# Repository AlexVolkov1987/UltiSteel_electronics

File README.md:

# UltiSteel_electronics
Electronics update for Ulti Steel 3D printer

------

:warning: Автор не несет ответственности за неправильную сборку, выбор комплектующих и любую порчу имущества и здоровья, вызванную эксплуатацией описываемых плат.

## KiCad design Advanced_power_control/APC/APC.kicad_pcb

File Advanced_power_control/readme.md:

# Модуль управления и мониторинга питания принтера

## Описание

### Функции:

- Включение принтера с помощью тактовой кнопки включение
- Выключение принтера по команде с платы управления принтера
- Выключение принтера с помощью тактовой кнопки включения
- Аварийное отключение принтера по команде с платы управления принтера
- Аварийное отключение принтера с помощью внешней кнопки
- Аварийное отключение принтера по КЗ или потере напряжения в линии питания 12/24В

### Разъемы:

- 220_IN - высоковольтный вход модуля. Должен всегда находиться под напряжением
- 220_OUT - управляемый выход модуля. К нему подключается высоковольтный вход блока питания принтера
- POWER_BUTTON - тактовая кнопка для включения/выключения модуля
- POWER_LED - индикация наличия питания на выходе блока питания принтера.
- STATUS_LED - индикация состояния принтера  
- EM_STOP - тактовая кнопка аварийной остановки. Должна быть нормально замкнутой. В случае отсутствия кнопки, для нормальной работы модуля необходимо установить перемычку EM_INT.
- 12/24 V_IN - мониторинг низковольтного выхода блока питания принтера
- CMD_IN - вход управления модулем от управляющей платы принтера.
- CMD_OUT - выход модуля для передачи информации на управляющую плату принтера

### Описание работы:

#### Установка

Установка модуля производится согласно схеме подключения ниже:

Если установка модуля выполнена корректно, то при подаче питания 220В модуль выдаст два коротких звуковых сигнала и включит индикатор STATUS_LED на 5 секунд. В дальнейшем индикатор STATUS_LED будет включаться на 1 секунду каждые 10с в качестве признака состояния сна модуля.

#### Первое включение (по нажатию тактовой кнопки POWER_BUTTON)

Включение модуля производится удержанием тактовой кнопки включения в течение 3-4с.  Модуль выдаст короткий звуковой сигнал и напряжение 220В будет подано на вход блока питания принтера. После этого индикатор STATUS_LED начнет мигать 1 раз в секунду. Таким образом, модуль перешел из состояния сна с состояние ожидания.

В течение минуты после подачи питания управляющая плата принтера должна подать напряжение на разъем модуля CMD_IN. Если этого не произойдет - модуль отключит подачу питания на вход блока питания принтера, выдаст три звуковых сигнала и перейдет из состояния ожидания в состояние сна.

При появлении напряжения на разъеме CMD_IN во время нахождения модуля в состоянии ожидания модуль выдаст один короткий звуковой сигнал, а индикатор  STATUS_LED будет светиться непрерывно. Модуль при этом перейдет в состояние активности.

! В процессе включения и выключения, а так же работы индикатор POWER_LED может включаться и выключаться с запаздыванием, поскольку он отображает наличие напряжения на выходе блока питания принтера и никак не управляется модулем.

#### Выключение (по нажатию кнопки POWER_BUTTON)

 При кратковременном нажатии кнопки POWER_BUTTON модуль управления питанием активирует выход CMD_OUT. Прошивка материнской платы должна использовать этот факт как выполнение последовательности команд по остановке печати, охлаждению хотэнда и снятию сигнала активности с входа CMD_IN.

Если плата снимает напряжение с входа CMD_IN, модуль выдаст двойной короткий звуковой сигнал и через 10с снимет напряжение с блока питания принтера, перейдя в состояние сна.

#### Выключение (по удержанию кнопки POWER_BUTTON)

При удержании кнопки POWER_BUTTON в течение 5-6с модуль снимает напряжение с блока питания принтера и переходит в состояние сна

#### Выключение по команде M81

Управляющая плата при выполнении команды M81 должна снять напряжение с входа CMD_IN модуля. Реакция модуля будет такой же как в варианте выключения по нажатию кнопки POWER_BUTTON.

#### Аварийное выключение по размыканию кнопки EM_STOP

При размыкании кнопки EM_STOP модуль немедленно снимает питание с блока питания принтера. Индикатор STATUS_LED при этом мигает с частотой 3 раза в секунду.

Также блокируется включение принтера по нажатию кнопки POWER_BUTTON. Для снятия блокировки необходимо замкнуть контакты кнопки  EM_STOP. Модуль при этом перейдет в состояние сна.

#### Аварийное выключение по потере напряжения 12/24В

Если в режиме активности на вход 12/24 V_IN не поступает напряжение с блока питания принтера (КЗ или выход из строя блока питания принтера), модуль немедленно снимает напряжение с входа блока питания принтера и выдает три длинных звуковых сигнала.  Индикатор STATUS_LED при этом мигает с частотой 3 раза в секунду.

Также блокируется включение принтера по нажатию кнопки POWER_BUTTON. Для снятия блокировки необходимо полностью обесточить модуль на 30-60сек.

### Список основных компонентов:

- ATMEGA164PA-AUR - микроконтроллер

- G5LE-14-DC5 - силовое реле

- LTV-817A - опторазвязка

- DG126-5.0-03P-14-00AH - клеммник

- IRM-03-5 - изолированный источник питания

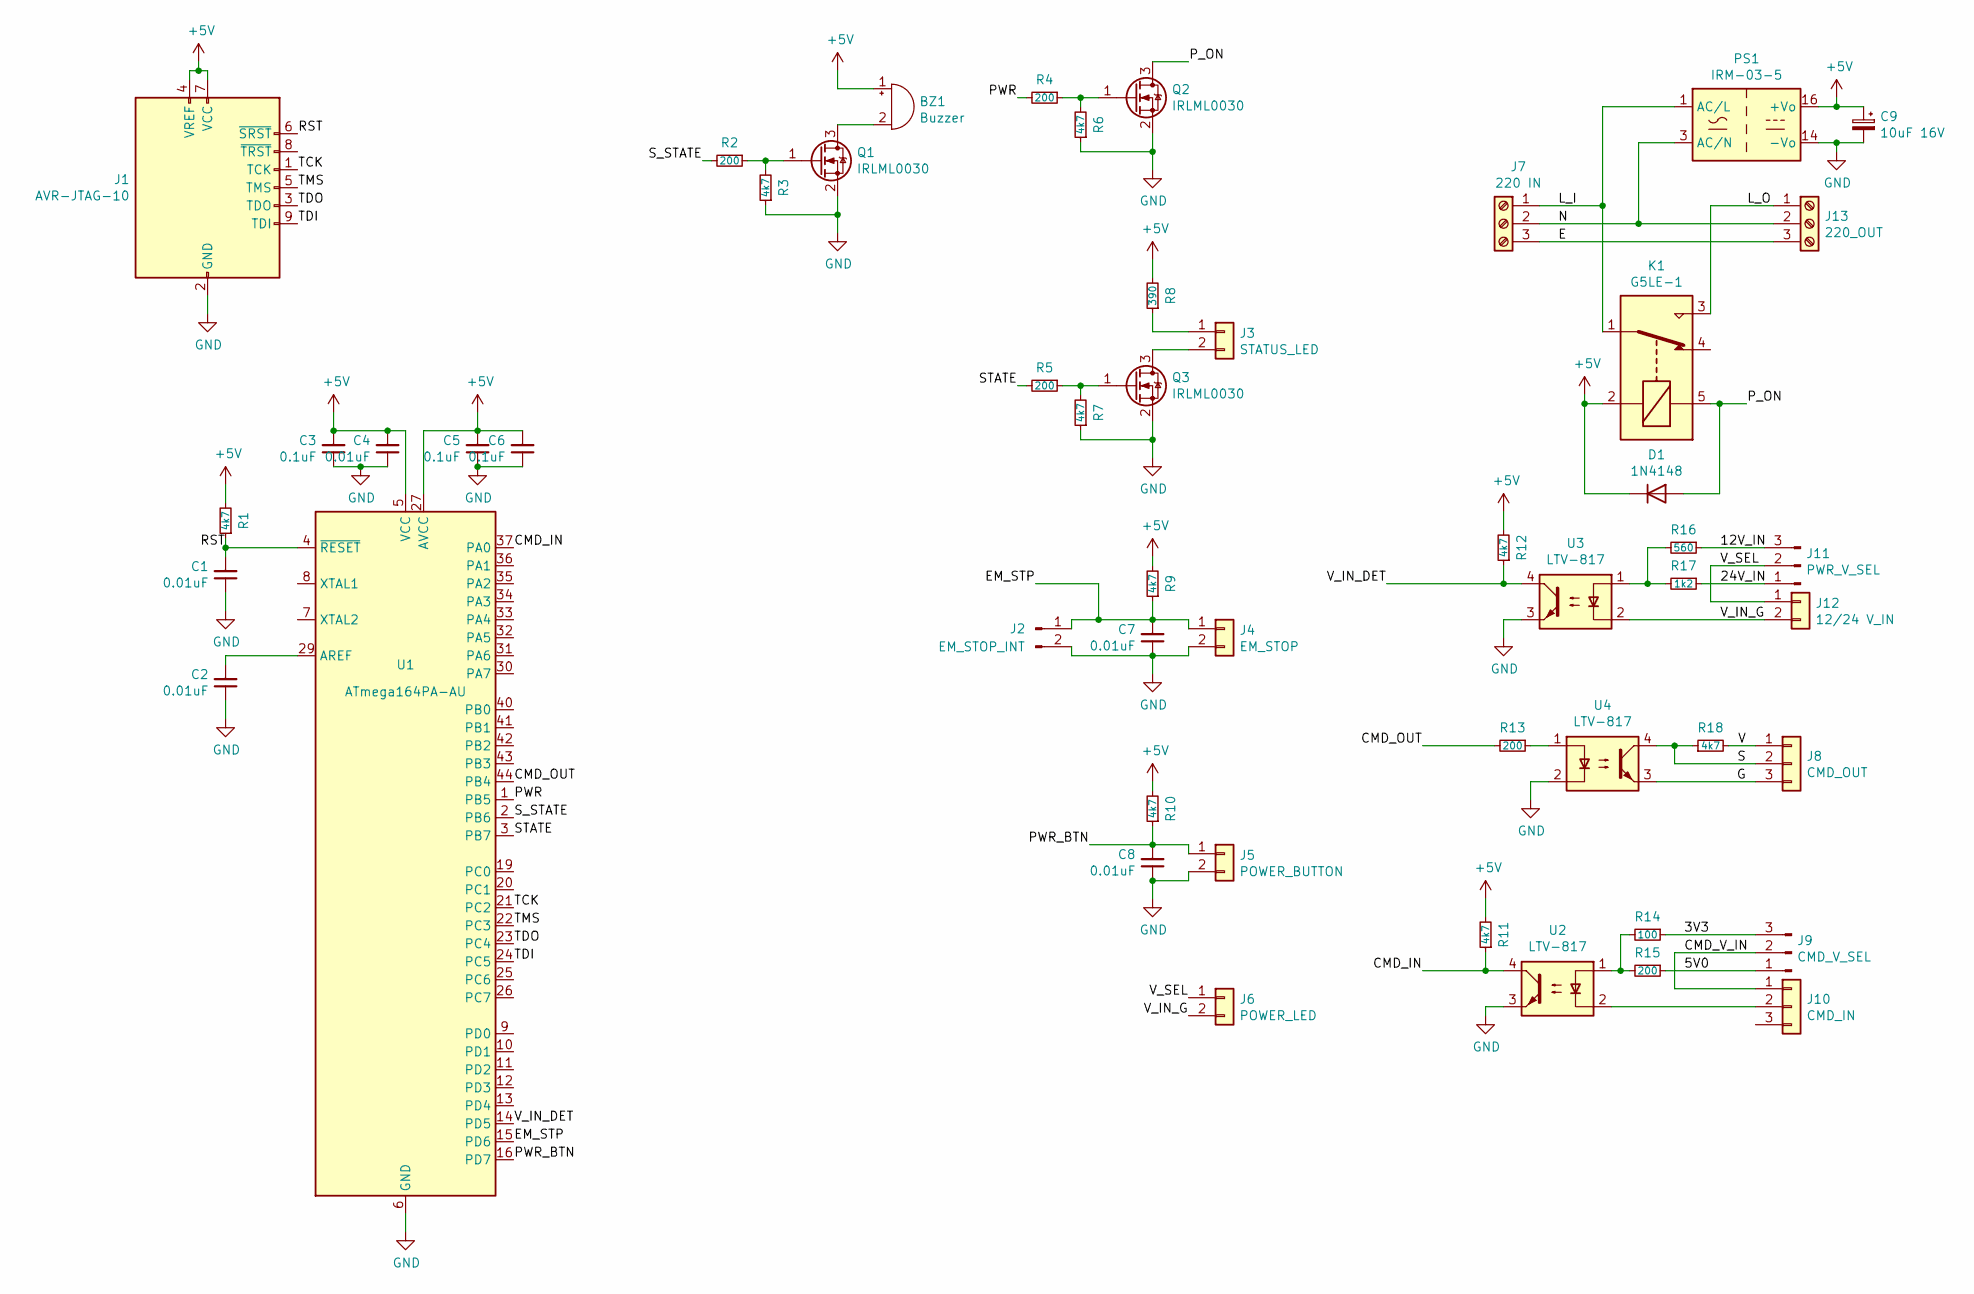
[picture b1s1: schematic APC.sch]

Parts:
BZ1: Buzzer; Buzzer_12x9.5RM7.6
C1, C2, C4, C7, C8: 0.01uF; C_0805_2012Metric_Pad1.15x1.40mm_HandSolder
C3, C5, C6: 0.1uF; C_0805_2012Metric_Pad1.15x1.40mm_HandSolder
C9: 10uF 16V; CP_EIA-3528-21_Kemet-B_Pad1.50x2.35mm_HandSolder
D1: 1N4148; D_DO-35_SOD27_P7.62mm_Horizontal
J1: AVR-JTAG-10; PinHeader_2x05_P2.54mm_Vertical
J2: EM_STOP_INT; PinHeader_1x02_P2.54mm_Vertical
J3: STATUS_LED; JST_EH_B2B-EH-A_1x02_P2.50mm_Vertical
J4: EM_STOP; JST_EH_B2B-EH-A_1x02_P2.50mm_Vertical
J5: POWER_BUTTON; JST_EH_B2B-EH-A_1x02_P2.50mm_Vertical
J6: POWER_LED; JST_EH_B2B-EH-A_1x02_P2.50mm_Vertical
J7: 220 IN; TerminalBlock_RND_205-00013_1x03_P5.00mm_Horizontal
J8: CMD_OUT; JST_EH_B3B-EH-A_1x03_P2.50mm_Vertical
J9: CMD_V_SEL; PinHeader_1x03_P2.54mm_Vertical
J10: CMD_IN; JST_EH_B3B-EH-A_1x03_P2.50mm_Vertical
J11: PWR_V_SEL; PinHeader_1x03_P2.54mm_Vertical
J12: 12/24 V_IN; JST_EH_B2B-EH-A_1x02_P2.50mm_Vertical
J13: 220_OUT; TerminalBlock_RND_205-00013_1x03_P5.00mm_Horizontal
K1: G5LE-1; Relay_SPDT_Omron-G5LE-1
PS1: IRM-03-5; Converter_ACDC_MeanWell_IRM-03-xx_THT
Q1, Q2, Q3: IRLML0030; SOT-23
R1, R3, R6, R7, R9, R10, R11, R12, R18: 4k7; R_0805_2012Metric_Pad1.20x1.40mm_HandSolder
R2, R4, R5, R13, R15: 200; R_0805_2012Metric_Pad1.20x1.40mm_HandSolder
R8: 390; R_0805_2012Metric_Pad1.20x1.40mm_HandSolder
R14: 100; R_0805_2012Metric_Pad1.20x1.40mm_HandSolder
R16: 560; R_0805_2012Metric_Pad1.20x1.40mm_HandSolder
R17: 1k2; R_0805_2012Metric_Pad1.20x1.40mm_HandSolder
U1: ATmega164PA-AU; TQFP-44_10x10mm_P0.8mm
U2, U3, U4: LTV-817; DIP-4_W7.62mm

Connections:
+5V: BZ1.1 (-), C3.2, C4.2, C5.2, C6.2, C9.1, D1.1 (K), J1.4 (VREF), J1.7 (VCC), K1.2, PS1.16 (+Vo), R1.2, R8.2, R9.2, R10.2, R11.2, R12.2, U1.5 (VCC), U1.17 (VCC), U1.27 (AVCC), U1.38 (VCC); also elsewhere on the board
/3V3: J9.3, R14.1
/5V0: J9.1, R15.1
/12V_IN: J11.3, R16.1
/24V_IN: J11.1, R17.1
/CMD_IN: R11.1, U1.37 (PA0), U2.4
/CMD_OUT: R13.2, U1.44 (PB4)
/CMD_V_IN: J9.2, J10.1
/E: J7.3, J13.3
/EM_STP: C7.2, J2.1, J4.1, R9.1, U1.15 (PD6)
/G: J8.3, U4.3
/L_I: J7.1, K1.1, PS1.1 (AC/L)
/L_O: J13.1, K1.3
/N: J7.2, J13.2, PS1.3 (AC/N)
/PWR: R4.2, U1.1 (PB5)
/PWR_BTN: C8.2, J5.1, R10.1, U1.16 (PD7)
/P_ON: D1.2 (A), K1.5, Q2.3 (D)
/RST: C1.2, J1.6 (~SRST), R1.1, U1.4 (~RESET); also elsewhere on the board
/S: J8.2, R18.1, U4.4
/STATE: R5.2, U1.3 (PB7)
/S_STATE: R2.2, U1.2 (PB6)
/TCK: J1.1 (TCK), U1.21 (PC2); also elsewhere on the board
/TDI: J1.9 (TDI), U1.24 (PC5); also elsewhere on the board
/TDO: J1.3 (TDO), U1.23 (PC4); also elsewhere on the board
/TMS: J1.5 (TMS), U1.22 (PC3); also elsewhere on the board
/V: J8.1, R18.2
/V_IN_DET: R12.1, U1.14 (PD5), U3.4
/V_IN_G: J6.2, J12.2, U3.2
/V_SEL: J6.1, J11.2, J12.1
GND: C1.1, C2.1, C3.1, C4.1, C5.1, C6.1, C7.1, C8.1, C9.2, J1.2 (GND), J1.10 (GND), J2.2, J4.2, J5.2, PS1.14 (-Vo), Q1.2 (S), Q2.2 (S), Q3.2 (S), R3.1, R6.1, R7.1, U1.6 (GND), U1.18 (GND), U1.28 (GND), U1.39 (GND), U2.3, U3.3, U4.2; also elsewhere on the board
unnamed: BZ1.2 (+), Q1.3 (D)
unnamed: C2.2, U1.29 (AREF)
unnamed: J3.1, R8.1
unnamed: J3.2, Q3.3 (D)
unnamed: J10.2, U2.2
unnamed: Q1.1 (G), R2.1, R3.2
unnamed: Q2.1 (G), R4.1, R6.2
unnamed: Q3.1 (G), R5.1, R7.2
unnamed: R13.1, U4.1
unnamed: R14.2, R15.2, U2.1
unnamed: R16.2, R17.2, U3.1

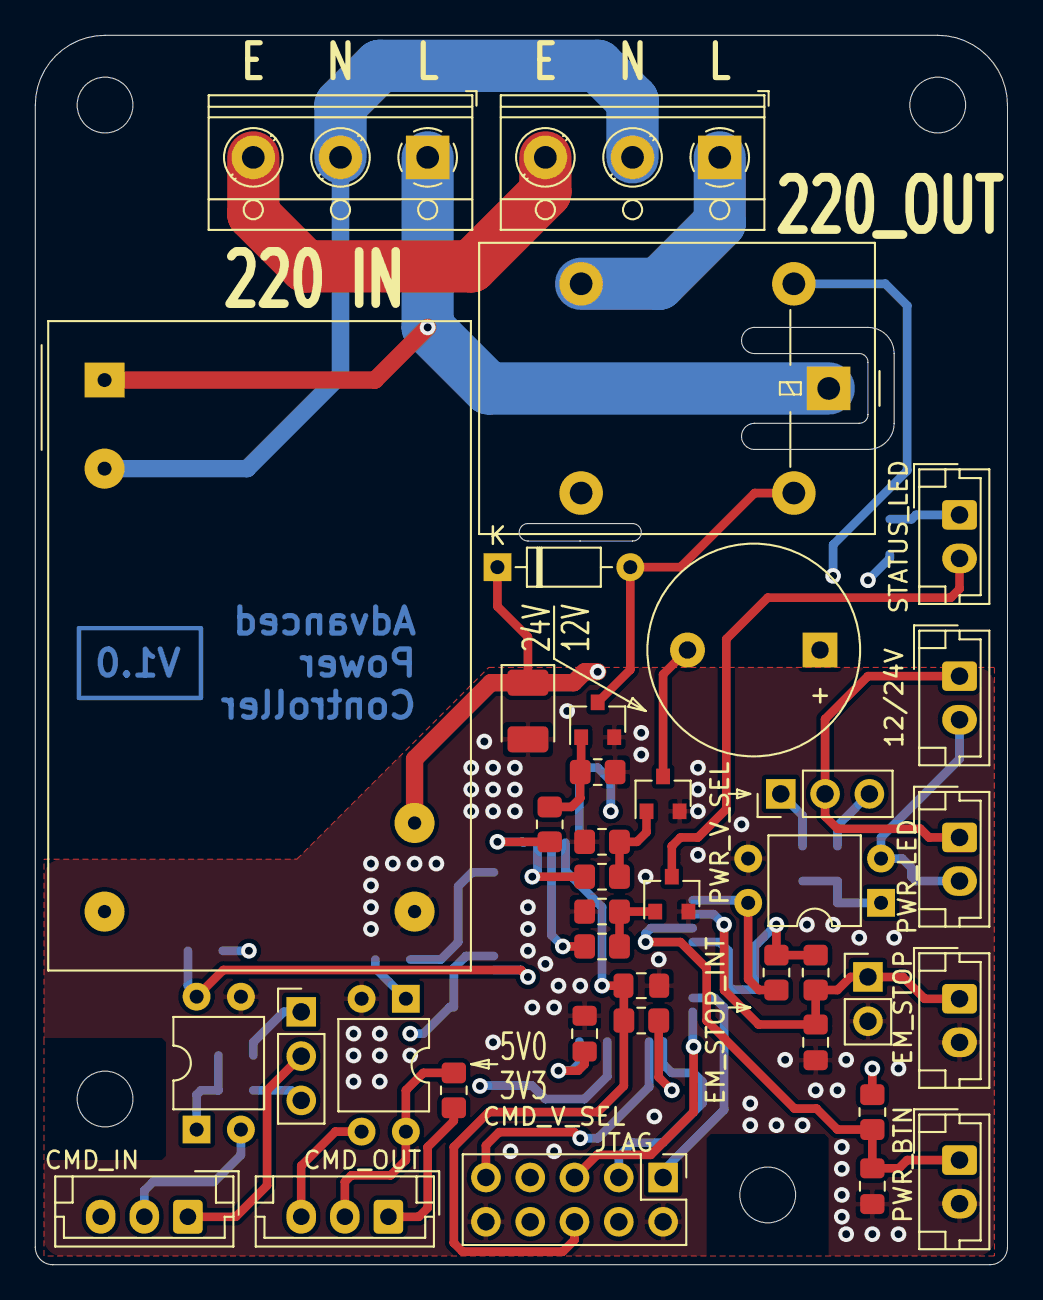
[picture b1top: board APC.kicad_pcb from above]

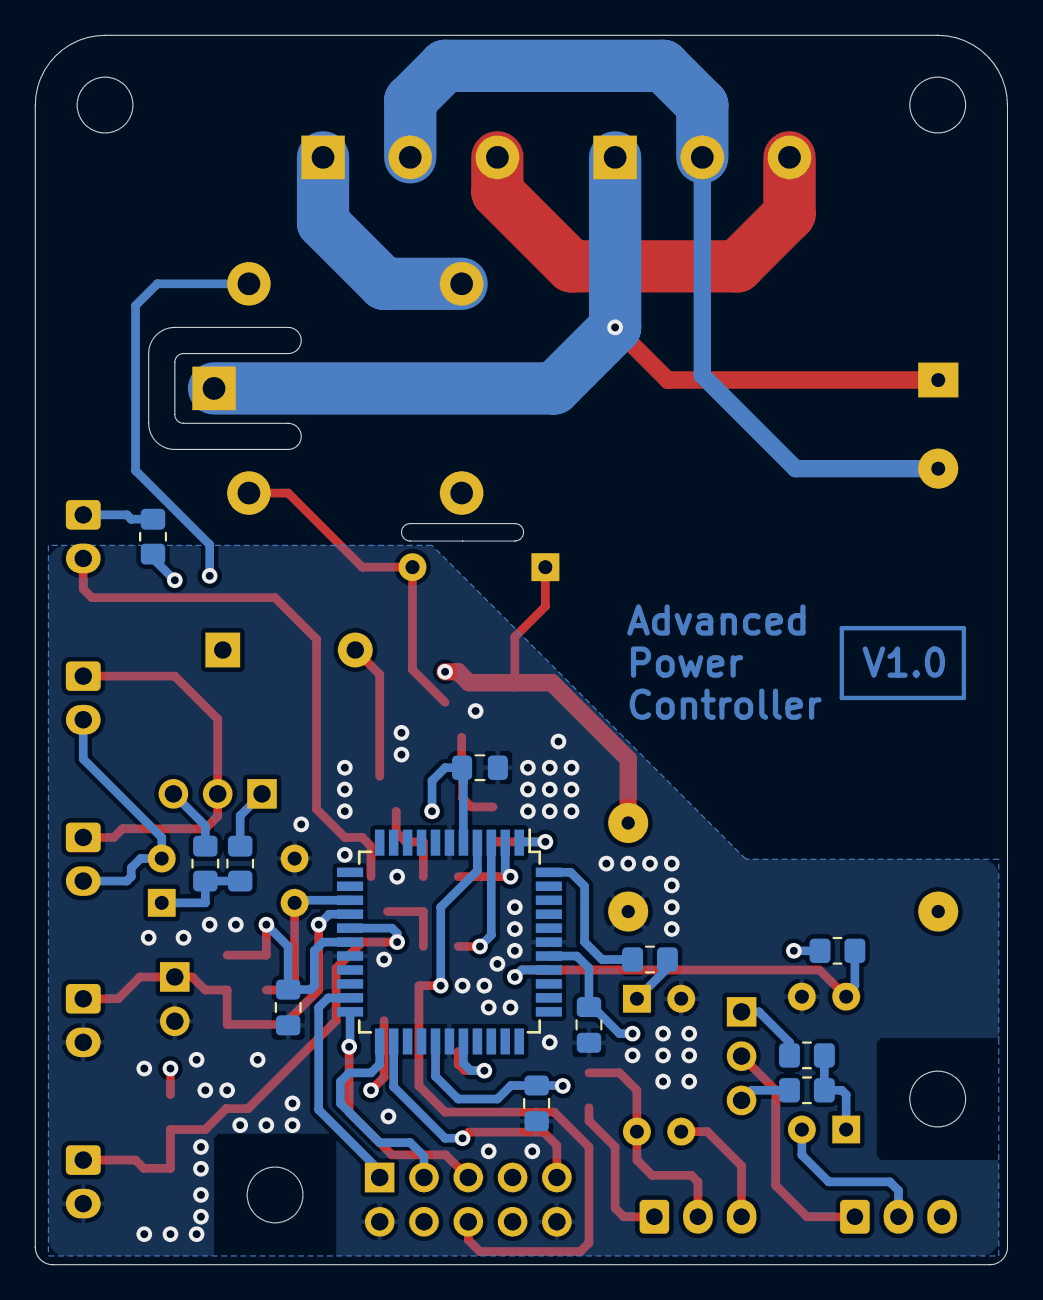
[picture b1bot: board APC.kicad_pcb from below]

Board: 4 copper layers, 55.8 x 70.5 mm, 51 parts (12 on the bottom side), 41 nets.

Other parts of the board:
JTAG: AVR-JTAG-10; PinHeader_2x05_P2.54mm_Vertical

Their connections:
+5V: JTAG.4, JTAG.7; also elsewhere on the board
/RST: JTAG.6; also elsewhere on the board
/TCK: JTAG.1; also elsewhere on the board
/TDI: JTAG.9; also elsewhere on the board
/TDO: JTAG.3; also elsewhere on the board
/TMS: JTAG.5; also elsewhere on the board
GND: JTAG.2, JTAG.10; also elsewhere on the board

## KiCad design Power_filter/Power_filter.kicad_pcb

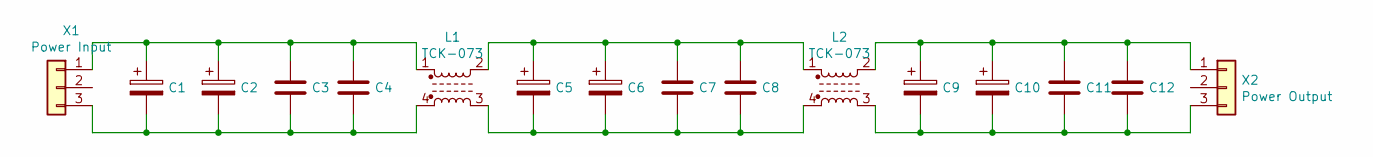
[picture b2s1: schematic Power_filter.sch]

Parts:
C1, C2, C5, C6, C9, C10: SH050M2200B7F-1636; CP_Radial_D16.0mm_P7.50mm
C3, C7, C11: RDER71H225K2K1H03B; C_Rect_L7.0mm_W3.5mm_P5.00mm
C4, C8, C12: RCER71H104K0M1H03A; C_Rect_L7.0mm_W2.5mm_P5.00mm
L1, L2: TCK-073; TRACO TCK-073
X1: Power Input; TerminalBlock_RND_205-00046_1x03_P5.00mm_Horizontal
X2: Power Output; TerminalBlock_RND_205-00046_1x03_P5.00mm_Horizontal

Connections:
unnamed: C1.1, C2.1, C3.1, C4.1, L1.1, X1.1
unnamed: C1.2, C2.2, C3.2, C4.2, L1.4, X1.3
unnamed: C5.1, C6.1, C7.1, C8.1, L1.2, L2.1
unnamed: C5.2, C6.2, C7.2, C8.2, L1.3, L2.4
unnamed: C9.1, C10.1, C11.1, C12.1, L2.2, X2.1
unnamed: C9.2, C10.2, C11.2, C12.2, L2.3, X2.3

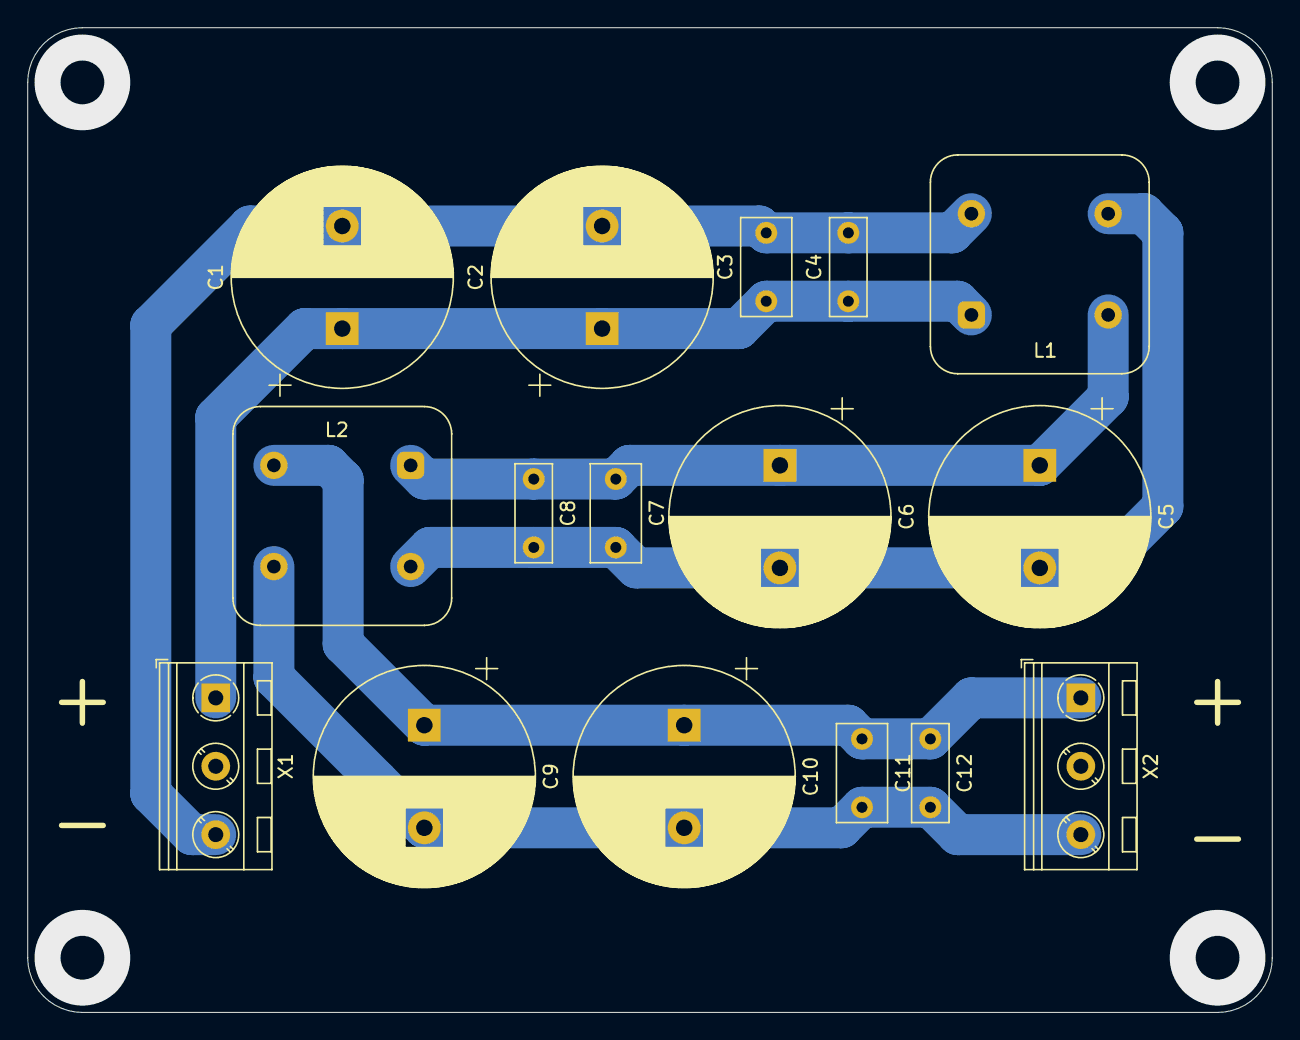
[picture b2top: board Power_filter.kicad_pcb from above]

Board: 2 copper layers, 91.0 x 72.0 mm, 16 parts (0 on the bottom side), 6 nets.

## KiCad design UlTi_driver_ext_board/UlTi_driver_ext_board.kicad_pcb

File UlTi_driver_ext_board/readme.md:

## UlTi_driver_ext_board

Плата представляет собой модуль расширения, устанавливаемый на свободное место, предназначенное для установки драйвера мотора.

### Возможности платы:

- 1 канал управления, включённый по умолчанию;
- 2 канала управления, выключенных по умолчанию;
- Максимальная нагрузка на канал - 1А;
- Максимальное напряжение питания  двигателей принтера  - 24В.

### Принцип работы:

Плата использует три линии связи с процессором материнской платы, которые соответствуют линиям **EN**, **STEP**, **DIR** платы драйвера мотора. Линии **EN** соответствуе выход **!FAN**, **STEP** - **FAN1**, **DIR** - **FAN2**. 

Ко всем трем линиям подключены маломощные MOSFET транзисторы типа **IRLML6344** или аналогичных с минимальным пороговым напряжением затвора и приемлемыми характеристиками канала при напряжении на затворе 3.3 - 5.0В.

Несмотря на то, что по документации подобные транзисторы рассчитаны на ток 4-5А через канал, я не рекомендую превышать значение 1А, поскольку у применяемых транзисторов минимальное охлаждение корпуса. Таким образом, подключаемая к каждому каналу управления может потреблять не более 12Вт при напряжении питания моторов принтера 12В и 24Вт при напряжении питания моторов принтера 24В. В эти значения укладываются как светодиодные ленты длиной 1М, так и большинство кулеров охлаждения.

Канал 1 (**!FAN**) при включении питания принтера будет всегда включен. Это удобно для подключения подсветки рабочей зоны или охлаждения электроники принтера. Каналы 2 и 3 (**FAN1**, **FAN2**) при подаче питания выключены. После запуска управляющей программы принтера состояние каналов может быть изменено.

Каналы **FAN1** и **FAN2** можно использовать в режиме ШИМ для регулирования выдаваемой в нагрузку мощности, канал **!FAN** рекомендуется использовать только в режиме вкл/выкл.

### Конфигурация ПО принтера:

Поскольку на принтерах может быть использовано разное ПО и разные материнские платы, я не могу указывать все варианты конфигурирования. Здесь будут рассмотрены только варианты подключения к платам Bigtreetech SKR 1.3 и MKS GenL V2 с прошивкой Klipper. 

#### Bigtreetech SKR 1.3

```
#-----------PINOUT-----------

#EN	P0.10	!FAN

#STEP	P0.1	FAN1

#DIR	P0.0	FAN2

#----------------------------

#!FAN config as output pin

#

#[output_pin light]

#pin: P0.10

#pwm: false

#value: 1.0

#shutdown_value: 1.0

#----------------------------

#FAN1 config as output pin

#

#[output_pin firstfan]

#pin: P0.1

#pwm: true

#value: 0.5

#shutdown_value: 1.0

#cycle_time: 0.01

#----------------------------

#FAN1 config as generic fan

#

#[fan_generic firstfan]

#pin: P0.1

#max_power: 1.0

#shutdown speed: 1.0

#cycle_time: 0.01

#----------------------------
```

#### MKS GenL V2

```
#-----------PINOUT-----------

#EN	ar30	!FAN

#STEP	ar36	FAN1

#DIR	ar34	FAN2

#----------------------------

#!FAN config as output pin

#

#[output_pin light]

#pin: ar30

#pwm: false

#value: 1.0

#shutdown_value: 1.0

#----------------------------

#FAN1 config as output pin

#

#[output_pin firstfan]

#pin: ar36

#pwm: true

#value: 0.5

#shutdown_value: 1.0

#cycle_time: 0.01

#----------------------------

#FAN1 config as generic fan

#

#[fan_generic firstfan]

#pin: ar36

#max_power: 1.0

#shutdown speed: 1.0

#cycle_time: 0.01

#----------------------------
```

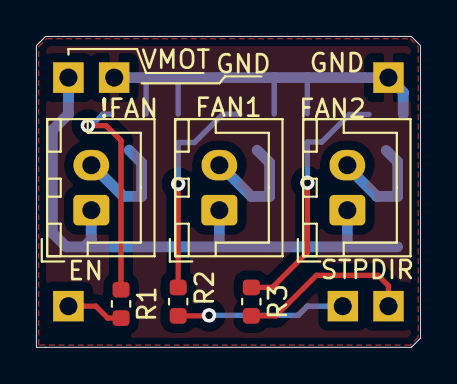
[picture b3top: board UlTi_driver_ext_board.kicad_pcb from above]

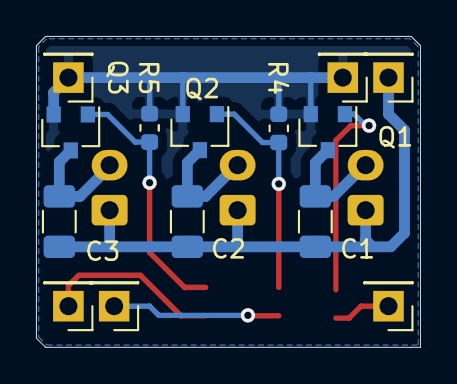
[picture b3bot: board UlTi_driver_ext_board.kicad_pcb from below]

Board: 2 copper layers, 21.3 x 17.3 mm, 20 parts (14 on the bottom side), 11 nets.

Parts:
!FAN: Conn_01x02; JST_XH_B2B-XH-A_1x02_P2.50mm_Vertical
C1, C2, C3: C_Small; C_1206_3216Metric
DIR: Conn_01x01_Male; PinHeader_1x01_P2.54mm_Vertical
EN: Conn_01x01_Male; PinHeader_1x01_P2.54mm_Vertical
FAN1, FAN2: Conn_01x02; JST_XH_B2B-XH-A_1x02_P2.50mm_Vertical
GND: Conn_01x01_Male; PinHeader_1x01_P2.54mm_Vertical
GND#2: Conn_01x01_Male; PinHeader_1x01_P2.54mm_Vertical
Q1, Q2, Q3: IRLML0030; SOT-23
R1, R2, R3: 47; R_0603_1608Metric
R4, R5: 10k; R_0603_1608Metric
STP: Conn_01x01_Male; PinHeader_1x01_P2.54mm_Vertical
VMOT: Conn_01x01_Male; PinHeader_1x01_P2.54mm_Vertical

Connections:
/fan0: EN.1, R1.2
/fan1: R2.2, STP.1
/fan2: DIR.1, R3.2
/gnd: GND.1, GND#2.1, Q1.2, Q2.2, Q3.2, R4.2, R5.2
/pwr: !FAN.1, C1.2, C2.2, C3.2, FAN1.1, FAN2.1, VMOT.1
unnamed: !FAN.2, C1.1, Q1.3
unnamed: C2.1, FAN1.2, Q2.3
unnamed: C3.1, FAN2.2, Q3.3
unnamed: Q1.1, R1.1
unnamed: Q2.1, R2.1, R4.1
unnamed: Q3.1, R3.1, R5.1

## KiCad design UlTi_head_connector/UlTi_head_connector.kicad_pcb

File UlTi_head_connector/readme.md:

## UlTi_head_connector

### Возможности платы

Для разработки платы за основу была взята плата от разработчиков принтера Ulti Steel. По сравнению с оригинальным вариантом сокращено количество проводов для подключения и уменьшен ассортимент используемых разъемов для подключения периферии.

Реализованы следующие возможности:

- Подключение нагревательного элемента через разъем XT-30;
- Подключение термистора через разъем JST XH 2.54;
- Подключение кулера обдува радиатора хотэнда через разъем JST XH 2.54;
- Подключение двух клеров обдува модели через разъемы JST XH 2.54.
- Подключение к материнской плате принтера всего 6 проводами.

### Принцип работы

Плата представляет собой простой переходник с проводов на разъемы. Уменьшение числа проводов для подключения платы к материнской плате принтера достигнуто за счет того, что + питания кулеров и нагревателя хотэнда - это одна и та же линия питания. А потребление кулеров по сравнению с нагревателем хотэнда незначительно. 

В связи с этим было принято решение провести к плате принтера 2 провода (+ и - нагревателя хотэнда) сечением 0.75мм^2 (родной провод нагревателя хотэнда), а для подключения кулеров использовать 2 провода сечением 0.2мм^2, подключаемых к материнской плате в разъемы, указанные в руководстве по сборке принтера Ulti Steel. Термистор подключается в свое гнездо на материнской плате так же двумя проводами сечением 0.2мм^2. 

### Подключение

Для корректного подключения с плате Bigtreetech SKR 1.3 следует использовать схему, приведенную в файле **Connection to skr.pdf**, который находится в папке **pdf**.

Подключение проводится только при полностью обесточенном принтере.

:warning: ​После подключения платы перед подачей питания настоятельно рекомендуется перепроверить правильность подключения.

:warning: Плата изолируется от алюминиевой пластины крепления кулеров обдува модели путем обрезания выводов разъемов заподлицо и прокладки любого изолирующего листового материала между платой и пластиной.

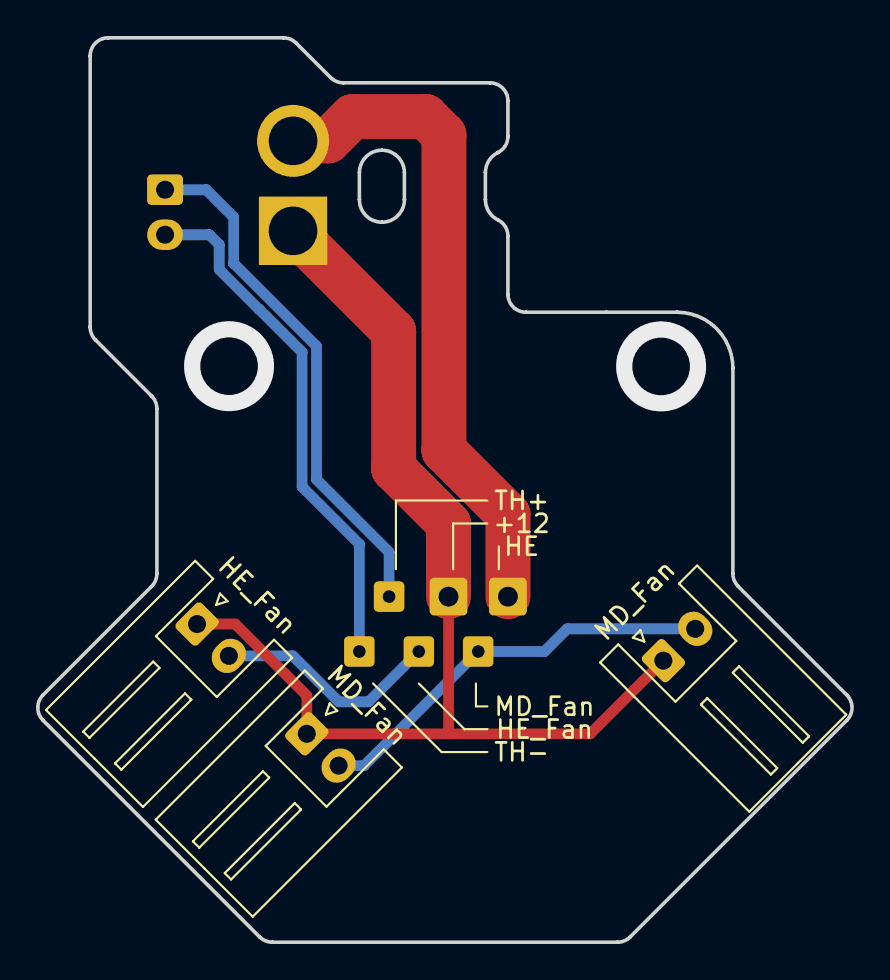
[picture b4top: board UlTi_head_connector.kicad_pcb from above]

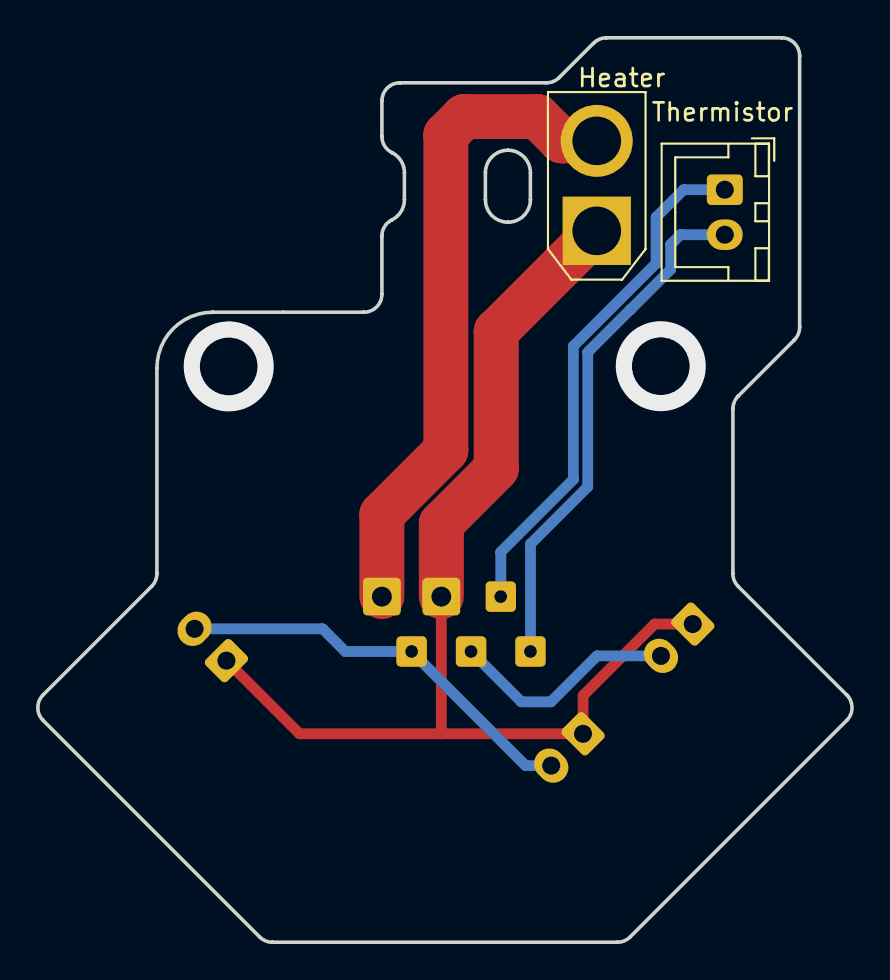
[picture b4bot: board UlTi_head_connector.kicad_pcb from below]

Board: 2 copper layers, 45.2 x 50.2 mm, 11 parts (2 on the bottom side), 6 nets.

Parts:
+12: Conn_01x01; SolderWire-0.5sqmm_1x01_D0.9mm_OD2.1mm
HE: Conn_01x01; SolderWire-0.5sqmm_1x01_D0.9mm_OD2.1mm
HE_Fan: Conn_01x02; JST_XH_S2B-XH-A_1x02_P2.50mm_Horizontal
HE_Fan#2: Conn_01x01; SolderWire-0.15sqmm_1x01_D0.5mm_OD1.5mm
Heater: Conn_01x02; AMASS_XT30U-F_1x02_P5.0mm_Vertical
MD_Fan: Conn_01x02; JST_XH_S2B-XH-A_1x02_P2.50mm_Horizontal
MD_Fan#2: Conn_01x02; JST_XH_S2B-XH-A_1x02_P2.50mm_Horizontal
MD_Fan#3: Conn_01x01; SolderWire-0.15sqmm_1x01_D0.5mm_OD1.5mm
TH+: Conn_01x01; SolderWire-0.15sqmm_1x01_D0.5mm_OD1.5mm
TH-: Conn_01x01; SolderWire-0.15sqmm_1x01_D0.5mm_OD1.5mm
Thermistor: Conn_01x02; JST_XH_B2B-XH-A_1x02_P2.50mm_Vertical

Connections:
/+PWR: +12.1, HE_Fan.1, Heater.1, MD_Fan.1, MD_Fan#2.1
/+th: TH+.1, Thermistor.1
/-HE_fan: HE_Fan.2, HE_Fan#2.1
/-Heater: HE.1, Heater.2
/-MD_fans: MD_Fan.2, MD_Fan#2.2, MD_Fan#3.1
/-th: TH-.1, Thermistor.2

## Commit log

2021-01-16 Initial Commit
    Добавлены все файлы проектов платы расширения и платы головы
2021-01-20 modify readme, add files
2021-03-15 add test power_filter
2021-03-17 add gerbers
2021-04-27 add APC
2021-04-28 init schematic
2021-04-28 clean
2021-04-28 update schematic
2021-04-28 add some schematic features
2021-04-29 pcb routing
2021-04-29 update schematic and board
2021-04-30 minimize pcb size
2021-05-04 Update APC.kicad_pcb
    PreFinal correction
2021-05-04 Release 1.0
    Update pcb
    Add assembly pdf-files
    Add gerber files
2021-05-04 some changes
    Change vias size fo jlcpcb
    Add gerbers in zip archive
2021-05-26 PDF correction
    Corrected values position on assembly
    Add BOM
2021-05-27 add firmware folder
    Init with atmel studio
2021-05-28 major changes
    - split readme.md
    -add isolator.dxf
